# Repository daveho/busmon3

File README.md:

# busmon3: Breadboard-friendly 16 bit hex display

`busmon3` is a 16 bit hex display designed to plug into standard 830 contact solderless breadboards.  It's useful for microcomputer projects and similar because it allows you to see the value being driven on a 16 bit bus.

Obligatory action shot (click for full size):

I got the idea from Quinn Dunki's [HexOut](http://quinndunki.com/blondihacks/?p=610) project.

The design is fairly brute force, but it does work.  The TQFN44 package of the atmega164a has 0.8mm pitch, which isn't too bad to hand-solder.  I have ordered boards from both [OSHPark](https://oshpark.com/) and [Seeed Studio](https://www.seeedstudio.com/fusion_pcb.html) and they work fine.

Note that the data inputs are pulled high (to VCC) by the atmega164a's internal pullup resistors.  You could change this in the firmware if you felt like it (e.g., because your bus already has external pullup or pulldown resistors.)

Also note that the board (1) is designed to sit at the top of an 830 contact breadboard, (2) assumes that VCC are GND are available on the breadboard's bus strips, and (3) assumes that the bottom bus strip is VCC.

# Parts needed

* atmega164a (TQFN44 package)
* 4 DIP14 package common anode 7 segment LED displays (MAN3620A, LTS-4910AHR, or similar)
* 4 SOT-23 MMBT3906 transistors
* 1 0.1uF 0805 ceramic capacitor (for decoupling)
* 7 270 Ohm 0805 resistors (the schematic shows 330 Ohm, but the displays are driven at 1/4 duty)
* 4 4.7K Ohm 0805 resistors
* 2 pin 0.1" male pin header (for breadboard power connections)
* 6 pin 0.1" male pin header (AVR programming header)
* 16 pin 0.1" male pin header (for breadboard data connections)

You will need an AVR programmer to program the firmware to the atmega164a.

# License

All material is copyright (c) 2017–2019, [David Hovemeyer](mailto:david.hovemeyer@gmail.com).

The hardware design is made available under the [CERN Open Hardware License version 1.2](https://www.ohwr.org/project/cernohl/uploads/505f27c2a8a10e528b079be3c9d876c5/cern_ohl_v_1_2.txt).

The firmware is made available under the [MIT License](https://opensource.org/licenses/MIT).

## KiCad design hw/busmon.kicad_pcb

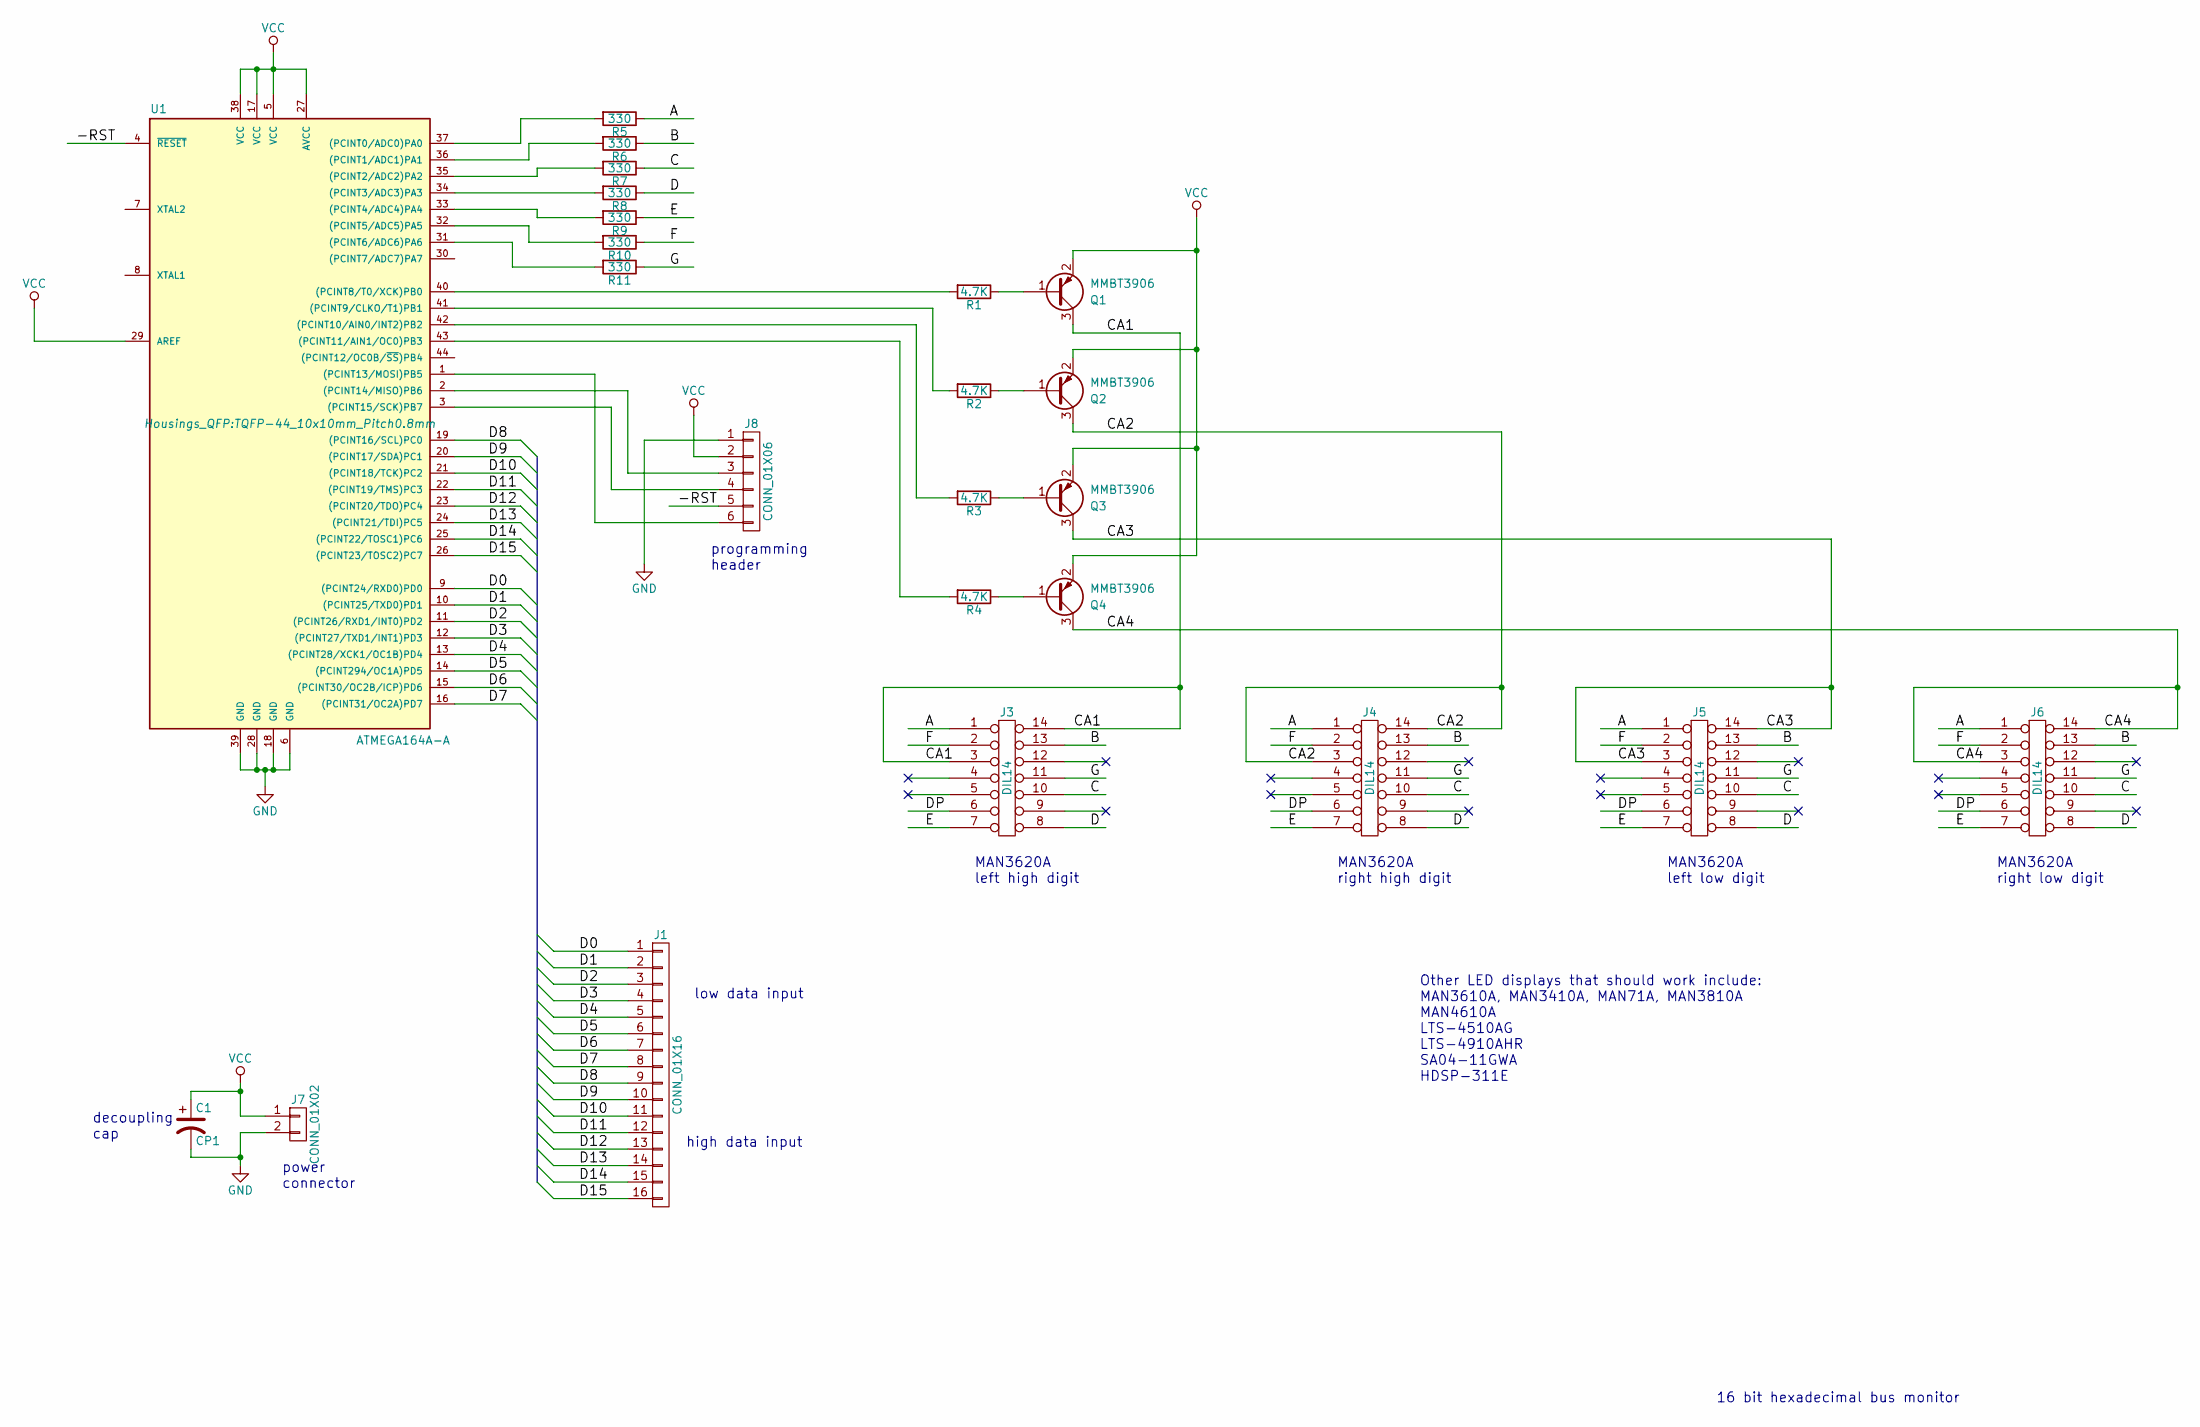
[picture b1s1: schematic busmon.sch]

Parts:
C1: CP1; CP_Tantalum_Case-A_EIA-3216-18_Hand
J1: CONN_01X16; Pin_Header_Straight_1x16_Pitch2.54mm
J3, J4, J5, J6: DIL14; DIP-14_W7.62mm
J7: CONN_01X02; Pin_Header_Straight_1x02_Pitch2.54mm
J8: CONN_01X06; Pin_Header_Straight_1x06_Pitch2.54mm
Q1, Q2, Q3, Q4: MMBT3906; SOT-23
R1, R2, R3, R4: 4.7K; R_0805_HandSoldering
R5, R6, R7, R8, R9, R10, R11: 330; R_0805_HandSoldering
U1: ATMEGA164A-A; TQFP-44_10x10mm_Pitch0.8mm

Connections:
/-RST: J8.5, U1.4 (~RESET)
/A: J3.1, J4.1, J5.1, J6.1, R5.1
/B: J3.13, J4.13, J5.13, J6.13, R6.1
/C: J3.10, J4.10, J5.10, J6.10, R7.1
/CA1: J3.3, J3.14, Q1.3 (C)
/CA2: J4.3, J4.14, Q2.3 (C)
/CA3: J5.3, J5.14, Q3.3 (C)
/CA4: J6.3, J6.14, Q4.3 (C)
/D: J3.8, J4.8, J5.8, J6.8, R8.1
/D0: J1.1, U1.9 ((PCINT24/RXD0)PD0)
/D1: J1.2, U1.10 ((PCINT25/TXD0)PD1)
/D2: J1.3, U1.11 ((PCINT26/RXD1/INT0)PD2)
/D3: J1.4, U1.12 ((PCINT27/TXD1/INT1)PD3)
/D4: J1.5, U1.13 ((PCINT28/XCK1/OC1B)PD4)
/D5: J1.6, U1.14 ((PCINT294/OC1A)PD5)
/D6: J1.7, U1.15 ((PCINT30/OC2B/ICP)PD6)
/D7: J1.8, U1.16 ((PCINT31/OC2A)PD7)
/D8: J1.9, U1.19 ((PCINT16/SCL)PC0)
/D9: J1.10, U1.20 ((PCINT17/SDA)PC1)
/D10: J1.11, U1.21 ((PCINT18/TCK)PC2)
/D11: J1.12, U1.22 ((PCINT19/TMS)PC3)
/D12: J1.13, U1.23 ((PCINT20/TDO)PC4)
/D13: J1.14, U1.24 ((PCINT21/TDI)PC5)
/D14: J1.15, U1.25 ((PCINT22/TOSC1)PC6)
/D15: J1.16, U1.26 ((PCINT23/TOSC2)PC7)
/DP: J3.6, J4.6, J5.6, J6.6
/E: J3.7, J4.7, J5.7, J6.7, R9.1
/F: J3.2, J4.2, J5.2, J6.2, R10.1
/G: J3.11, J4.11, J5.11, J6.11, R11.1
GND: C1.2, J7.2, J8.1, U1.6 (GND), U1.18 (GND), U1.28 (GND), U1.39 (GND)
unnamed: J8.3, U1.2 ((PCINT14/MISO)PB6)
unnamed: J8.4, U1.3 ((PCINT15/SCK)PB7)
unnamed: J8.6, U1.1 ((PCINT13/MOSI)PB5)
unnamed: Q1.1 (B), R1.1
unnamed: Q2.1 (B), R2.1
unnamed: Q3.1 (B), R3.1
unnamed: Q4.1 (B), R4.1
unnamed: R1.2, U1.40 ((PCINT8/T0/XCK)PB0)
unnamed: R2.2, U1.41 ((PCINT9/CLKO/T1)PB1)
unnamed: R3.2, U1.42 ((PCINT10/AIN0/INT2)PB2)
unnamed: R4.2, U1.43 ((PCINT11/AIN1/OC0)PB3)
unnamed: R5.2, U1.37 ((PCINT0/ADC0)PA0)
unnamed: R6.2, U1.36 ((PCINT1/ADC1)PA1)
unnamed: R7.2, U1.35 ((PCINT2/ADC2)PA2)
unnamed: R8.2, U1.34 ((PCINT3/ADC3)PA3)
unnamed: R9.2, U1.33 ((PCINT4/ADC4)PA4)
unnamed: R10.2, U1.32 ((PCINT5/ADC5)PA5)
unnamed: R11.2, U1.31 ((PCINT6/ADC6)PA6)
VCC: C1.1, J7.1, J8.2, Q1.2 (E), Q2.2 (E), Q3.2 (E), Q4.2 (E), U1.5 (VCC), U1.17 (VCC), U1.27 (AVCC), U1.29 (AREF), U1.38 (VCC)

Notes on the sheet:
MAN3620A left high digit
MAN3620A right high digit
16 bit hexadecimal bus monitor
power connector
low data input
MAN3620A left low digit
MAN3620A right low digit
high data input
decoupling cap
programming header
Other LED displays that should work include: MAN3610A, MAN3410A, MAN71A, MAN3810A MAN4610A LTS-4510AG LTS-4910AHR SA04-11GWA HDSP-311E

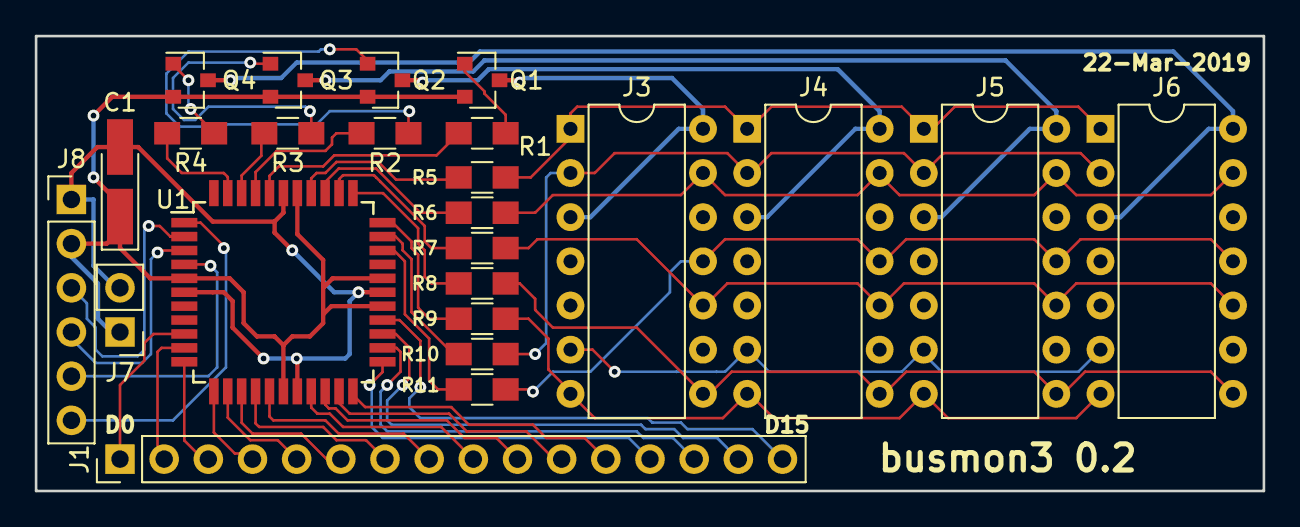
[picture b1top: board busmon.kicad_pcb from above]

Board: 2 copper layers, 70.6 x 26.2 mm, 24 parts (0 on the bottom side), 49 nets.

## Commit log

2017-06-12 initial checkin
2017-06-12 connected components
2017-06-12 getting ready for pcb
2017-06-12 associate footprints
2017-06-12 use SOT23-3 for transistors
2017-06-12 regenerate netlist
2017-06-12 use 1x16 header for data input
2017-06-12 label tweak
2017-06-12 use correct transistor pinout
2017-06-12 updated footprint associations
2017-06-12 fix transistor orientation
2017-06-12 initial component layout
2017-06-12 started routing power connections
2017-06-12 routing more signals
2017-06-12 routed more signals
2017-06-12 routed all signals
2017-06-12 routed a few missed signals
2017-07-10 test firmware, just turn all segments on
2017-07-11 implemented ISR for polling/display
2019-03-10 disable JTAG
    This was all that was needed to get the device
    completely working! The stuck low values
    were due to the JTAG hardware preventing
    using bits 2..5 of PORTC as inputs.
    Also did a bit of code refactoring and cleanup.
2019-03-10 converted project to KiCad 5
    Hopefully the PCB is still good.
2019-03-22 improve schematic, minor silkscreen fixes
2019-03-23 updated .gitignore
2019-04-01 get ready to make public
2019-04-01 added small version of picture
2019-04-18 photo of version 0.2
2019-04-18 mention Seeed Studio
2019-04-18 note about using 270 Ohm resistors
2019-04-19 slow refresh rate to reduce segment ghosting
